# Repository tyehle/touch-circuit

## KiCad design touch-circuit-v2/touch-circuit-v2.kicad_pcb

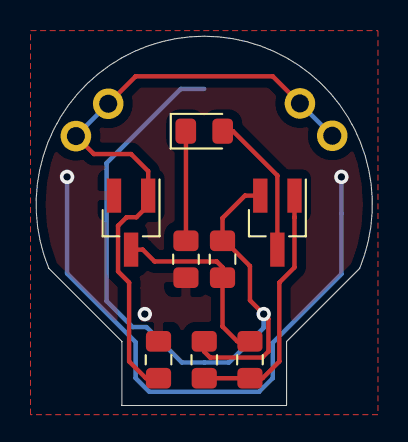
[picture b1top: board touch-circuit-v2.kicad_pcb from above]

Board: 2 copper layers, 18.7 x 20.5 mm, 9 parts (1 on the bottom side), 7 nets.

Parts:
BT1: Battery_Cell; BatteryHolder_LINX_BAT-HLD-012-SMT
C1: 10uF; C_0805_2012Metric_Pad1.15x1.40mm_HandSolder
D1: LED; LED_0805_2012Metric_Pad1.15x1.40mm_HandSolder
Q1: NMOS; SOT-23_Handsoldering
Q2: PMOS; SOT-23_Handsoldering
R1: 3.3M; R_0805_2012Metric_Pad1.15x1.40mm_HandSolder
R2: 56k; R_0805_2012Metric_Pad1.15x1.40mm_HandSolder
R3: 82k; R_0805_2012Metric_Pad1.15x1.40mm_HandSolder
R4: R_LED; R_0805_2012Metric_Pad1.15x1.40mm_HandSolder

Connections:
/Gate: Q1.1, R1.1
GND: BT1.2, Q1.2, R1.2, R4.2
unnamed: BT1.1, C1.1, Q2.2, R2.1
unnamed: C1.2, Q2.1, R3.1
unnamed: D1.1, R4.1
unnamed: D1.2, Q2.3
unnamed: Q1.3, R2.2, R3.2

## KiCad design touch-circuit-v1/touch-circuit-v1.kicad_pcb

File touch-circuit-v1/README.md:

# Touch Circuit v1

# Schematic

# LICENSE

This work is licensed under a [Creative Commons Attribution-NonCommercial-ShareAlike 4.0 International License](http://creativecommons.org/licenses/by-nc-sa/4.0/).

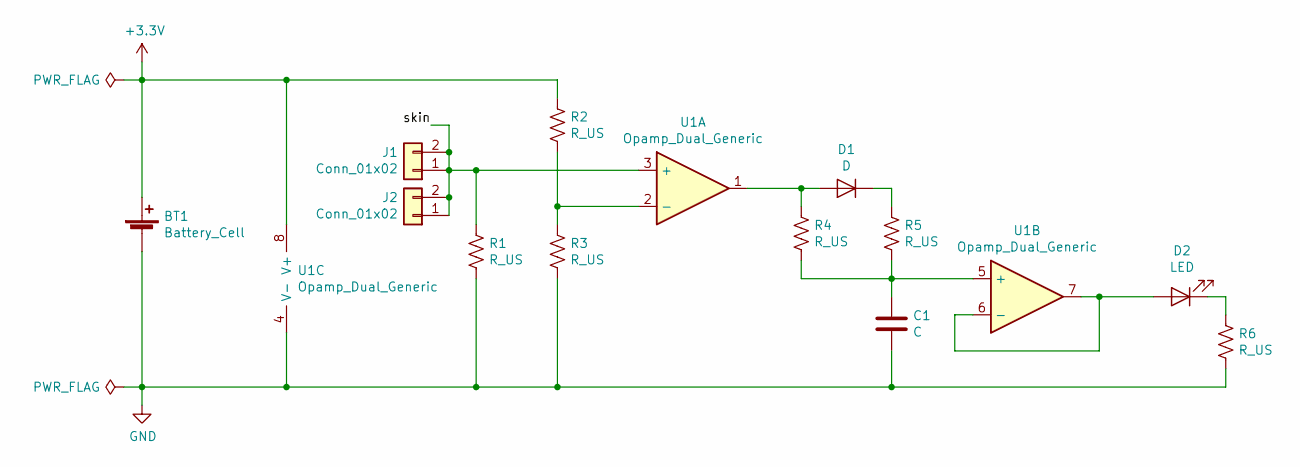
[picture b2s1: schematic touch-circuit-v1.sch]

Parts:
BT1: Battery_Cell; BatteryHolder_LINX_BAT-HLD-012-SMT
C1: C; C_0805_2012Metric_Pad1.15x1.40mm_HandSolder
D1: D; D_0805_2012Metric_Pad1.15x1.40mm_HandSolder
D2: LED; LED_0805_2012Metric_Pad1.15x1.40mm_HandSolder
J1, J2: Conn_01x02; PinHeader_1x02_P2.54mm_Vertical_nosilk
R1, R2, R3, R4, R5, R6: R_US; R_0805_2012Metric_Pad1.15x1.40mm_HandSolder
U1: Opamp_Dual_Generic; SO-8_5.3x6.2mm_P1.27mm

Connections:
+3V3: BT1.1 (+), R2.1, U1.8 (V+)
/skin: J1.1, J1.2, J2.1, J2.2, R1.1, U1.3 (+)
GND: BT1.2 (-), C1.2, R1.2, R3.2, R6.2, U1.4 (V-)
unnamed: C1.1, R4.2, R5.2, U1.5 (+)
unnamed: D1.1 (K), R5.1
unnamed: D1.2 (A), R4.1, U1.1
unnamed: D2.1 (K), R6.1
unnamed: D2.2 (A), U1.6 (-), U1.7
unnamed: R2.2, R3.1, U1.2 (-)

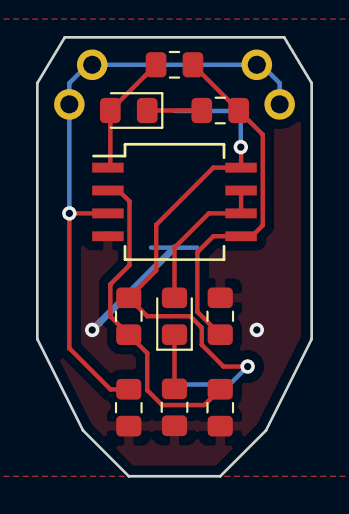
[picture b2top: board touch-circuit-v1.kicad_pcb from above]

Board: 2 copper layers, 15.2 x 24.4 mm, 13 parts (1 on the bottom side), 9 nets.

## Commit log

2020-01-28 add the falstad sim of the circuit
2020-01-28 base kicad project
2020-01-28 basic schematic
2020-01-28 add footprints
2020-01-28 add mounting holes
2020-01-29 add silk and update mounting footprints
2020-01-31 add gerbers and renders
2020-02-06 change the opamp module I'm using
2020-02-06 move the falstad file for v1
2020-02-06 add a v2 version of the circuit
2020-05-05 Fix svg links
2020-06-19 update schematic for high side jumper
2020-06-19 high side jumper
2020-06-19 reroute board
2020-06-19 add the mounting holes and clean up the fab layer
2020-06-19 add ty footprints
2020-06-19 update back silk
2020-06-19 add gerbers

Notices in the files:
touch-circuit-v1/touch-circuit-v1.kicad_pcb:
CC BY-NC-SA
